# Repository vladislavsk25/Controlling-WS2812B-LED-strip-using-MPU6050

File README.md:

# Virtual Water Tube – Realistic Tilt-Controlled Water Simulation   
**Author:** Vladislav Skachkov  
**Date:** November 2025  

### The “Virtual Waves” project  
A stunningly realistic glowing water simulation running on a **Raspberry Pi Pico** using an **MPU6050** accelerometer and a **WS2812B (NeoPixel) LED strip**.
When you tilt the board(sensor) left or right, the glowing “water” flows, bounces off the ends with perfect damping, and slowly settles.

[Link to the demo version of a project](https://www.youtube.com/watch?v=vVL3egFfj9s) 

### Features
- Dual-core design (100 Hz physics on Core 0, ~22 FPS visuals on Core 1)  
- Perfectly tuned physics: sensitivity, viscosity, wall bounce  
- Live ASCII art visualization in Serial Monitor  
- Beautiful automatic demo mode (sine wave) when no sensor is connected  
- Random shimmer effect for extra realism  

### Hardware 
- Raspberry Pi Pico (or Pico W)  
- Adafruit MPU6050 (or any MPU6050 breakout)  
- WS2812B LED strip (any length, 30 LEDs used in the current system)  
- External 5V power supply

### Wiring 

/Raspberry Pi Pico
	-3.3V(OUT) (pin 36)
	-GND (pin 38)

/MPU6050 
	-VCC → 3.3 V
	-GND → GND
	-SDA → GP4
	-SCL → GP5

/WS2812B strip
	-VCC  → 3.3V (1-2 A)
	-GND → Pico GND
	-DIN → 330Ω resistor → Pico GP11

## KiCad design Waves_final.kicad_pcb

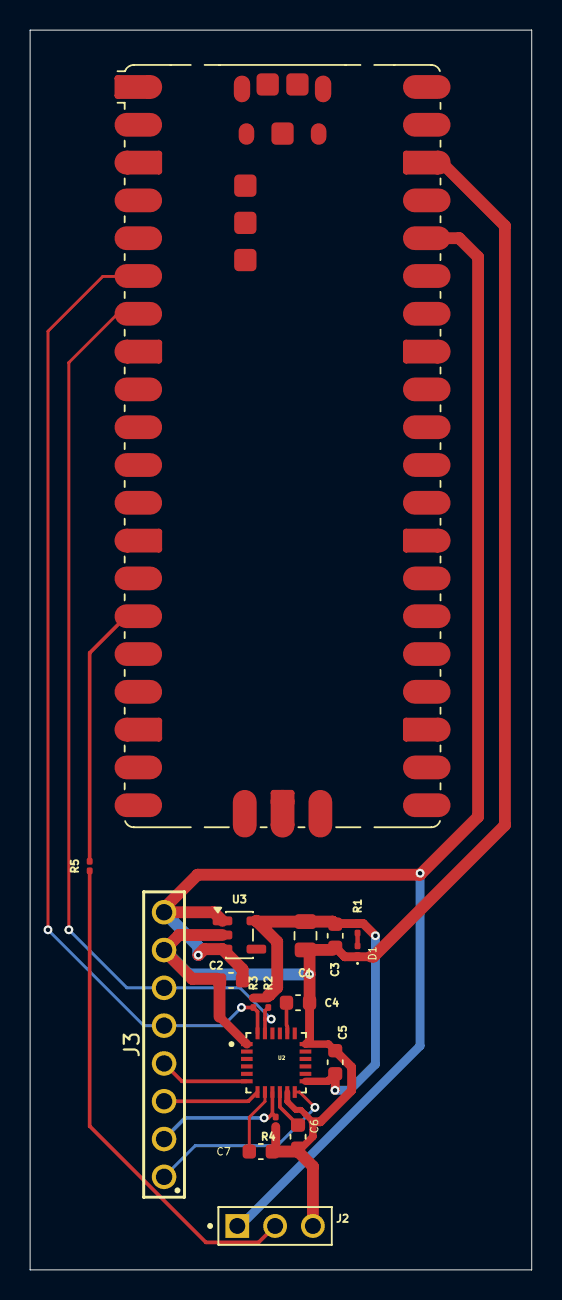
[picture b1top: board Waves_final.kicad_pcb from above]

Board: 2 copper layers, 33.7 x 83.3 mm, 18 parts (0 on the bottom side), 15 nets.

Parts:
C1: 10uF; C_0805_2012Metric
C2: 4.7uF; C_0603_1608Metric
C3, C5, C6: 0.1uF; C_0603_1608Metric
C4: 2200pF; C_0603_1608Metric
C7: 0.01uF; C_0603_1608Metric
D1: LED; LED_0201_0603Metric
J2: LED INPUT (3 pins); HARWIN_M20-9990345
J3: 6130XX11121_61300811121; 61300811121
R1: 1K; R_0201_0603Metric
R2, R3: 2.2K; R_0201_0603Metric
R4: 4.7K; R_0201_0603Metric
R5: 330; R_0201_0603Metric
U1: RASPBERRY_PI_PICO; RaspberryPi_Pico_SMD
U2: MPU-6050; QFN50P400X400X95-24N
U3: RT9193-33GB (3.3 LDO); SOT-23-5

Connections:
+3.3V: C1.1, C3.1, C5.1, R1.1, R2.1, R3.1, U2.13 (VDD), U3.5 (VOUT)
+5V: C2.1, J2.1, J3.8, U3.1 (VIN), U3.3 (EN)
/ADO: J3.2, R4.1, U2.9 (AD0)
/Din: J2.2, R5.2
/INT: J3.1, U2.12 (INT)
/SCL: J3.6, R2.2, U2.23 (SCL)
/SDA: J3.5, R3.2, U2.24 (SDA)
/XCL: J3.3, U2.7 (AUX_CL)
/XDA: J3.4, U2.6 (AUX_DA)
Earth: C1.2, C2.2, C3.2, C4.2, C5.2, C6.1, C7.2, D1.1 (K), J2.3, J3.7, R4.2, U2.1 (CLKIN), U2.11 (FSYNC), U2.18 (GND), U3.2 (GND)
unnamed: D1.2 (A), R1.2
unnamed: C4.1, U2.20 (CPOUT)
unnamed: U2.2 (NC), U2.3 (NC), U2.4 (NC), U2.5 (NC), U2.14 (NC), U2.15 (NC), U2.16 (NC), U2.17 (NC)
unnamed: C6.2, U2.10 (REGOUT)
unnamed: C7.1, U2.8 (VLOGIC)
